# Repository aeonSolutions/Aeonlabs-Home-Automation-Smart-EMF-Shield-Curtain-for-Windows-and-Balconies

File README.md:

[ ](https://discord.gg/hw3j3RwfJf)

**Navigation** | [AeonLabs Main Index](https://github.com/aeonSolutions/aeonSolutions/blob/main/aeonSolutions-Main-Index.md)  >>  [Open Hardware Electronics](https://github.com/aeonSolutions/PCB-Prototyping-Catalogue)   >>   [Home-Automation](https://github.com/aeonSolutions/PCB-Prototyping-Catalogue/tree/main/Home-Automation)  >>  [Safety & Health](https://github.com/aeonSolutions/AeonLabs-Safety-Health)     >>  Smart EMF Shield Curtain for Windows and Balconies

<p align="right">
 <a href="https://github-com.translate.goog/aeonSolutions/Aeonlabs-Home-Automation-Smart-EMF-Shield-Curtain-for-Windows-and-Balconies?_x_tr_sl=en&_x_tr_tl=nl&_x_tr_hl=en&_x_tr_pto=wapp">Change language</a> <br>
Last update 07-09-2024 <br> <br>
partially sponsored by <br> 
    
</p>

⚠️ **Start by reading the documentation first**. [Click here to open it](https://github.com/aeonSolutions/AeonLabs-Safety-Health/wiki) 

# Smart EMF Shield Curtain for Windows and Balconies

<p align="left"> 
  
<b>Status:</b>
 Hardware electronics are Fully tested and working. The first 🥇 release of the firmware code is now available. <br>
&nbsp; Looking for someone available to collaborate on the firmware coding. If you like this project and want faster development, prototyping, and testing consider a donation or sponsoring. thank you 🙏.
 </p>

<p align="center">  
   
</p>

## The problem
nowadays many are sensitive to electromagnetic frequency radiation mainly due to excessive exposure above natural and healthy limits. There are many solutions to mitigate exposure to this kind of radiation however none have the ability to collect EMF energy values directly from a window or access door to a balcony.

## The idea
This smart device is intended to be installed and fixed into a copper electromagnetic (EM) shield on any EM indoor window or balcony door. It has the main ability to collect EM sensor data from the curtain itself and send it to a public data repository, for instance, a #dataverse (see www.dataverse.org)

<p align="center">
   <br>
   <sup> Figure 1- Example of a window in a room where this Smart Device can be installed</sup>
</p>

## Total Cost of this Project
The total cost of this project to date is listed below:
- Work hours dedicated to this project: >300 w.h <br>
  This includes research and study about Bio EM RF, building this repository, and other useless miscellaneous online tasks. <br>
  hardware electronics assembly and testing, several times.
- Electronic components  >200 eur
- Aluminium Enclosure Case and other materials ~20 eur ( [buy one on AliExpress ](https://s.click.aliexpress.com/e/_DkqC3wL) )

<p align="center">

</p>

See [here](https://github.com/aeonSolutions/AeonLabs-Safety-Health) who sponsored, to this date, the Safety & Health project. 

<br>

## Important Information
The smart safety & health solution is for the kind of wireless aggression that behaves like ripples in a pond. For instance Wireless electromagnetic radios, including those found on smartphones, tablets, wifi routers at home, and many more.

**This smart device is not able to detect wireless aggressions targeted to a person's body and individual. For instance, using some kind of beam-forming device or technologies**. For example, Laser and laser-like kind of devices and kind of technologies. 

**When installing this smart solution, take action and be conscious that the aggression/aggressor may change to other types and kinds of "wireless devices" this smart device is unable to detect**.  

**Always use this smart device connected to a public data repository with LIVE data streams. At the same time, notify the authorities immediately and provide the web address link where the public data repository can be found**. Data repositories based on Harvard's www.dataverse.org are currently the most suited (not ideal) for the smart solution provided. 

**Be advised**

Known open data repositories partially compatible with these smart devices:
- www.dataverse.org [partial compatible] (open firmware provided here uses a dataverse repository API)
- www.figshare.com [partial compatible]
- www.datadryad.org [not compatible; no API]

<br>

<p align="center">
     <br>
 <sup> Figure 2 - 3D rendering in KiCad of the hardware electronics </sup>
</p>

<p align="center">
<strong> <a href="https://aeonsolutions.github.io/sponsor/em_radiation/">Interactive view of the PCB Layout</a> </strong> &nbsp;
  <strong> <a href="https://aeonsolutions.github.io/sponsor/em_radiation//circuit_schematic.html">Interactive view of the circuit schematic</a> </strong> <br>
 <sup>Click to view the latest revision</sup>
</p>

This device is designed to burn out every time an electromagnetic pulse, spark, or other EMF has a too-high energy. This way the victim can use the burnt device as evidence when presenting a complaint to the authorities.

stay safe.

<p align="center">
    <br>
 <sup> Figure 3 - Smart EM Device Already Assemble and ready to be installed on the Aluminium Enclosure</sup>
</p>

## Compatibility

<p align="center">

</p>

###  Status
  Hardware electronics are Fully tested and working. The first 🥇 release of the firmware code is now available.

[January 1, 2024] - The firmware 1.0.0 for Over the Air Updates is now released to the public. Goto the [releases section](https://github.com/aeonSolutions/Aeonlabs-Home-Automation-Smart-EMF-Shield-Curtain-for-Windows-and-Balconies/releases/tag/openFirmware) to learn more.  

<br>

## OEM Firmware code
The OEM version of the firmware code can be found in the folder **OEM firmware code**.  It has by default OTA updates, meaning the smart concrete curing device automatically updates it self when newer updated versions are made available here.  

This code uses my own ESP32 C++ class libraries to expedite the development of the code of ESP32 microcontrollers. The repository is located in the [open source software section](https://github.com/aeonSolutions/aeonlabs-ESP32-C-Base-Firmware-Libraries#readme).

#### Send the collected sensor data to this repository
On this repository, there's a special folder, named [datasets](https://github.com/aeonSolutions/AeonLabs-Safety-Health/tree/main/Measurements/datasets), where anyone is able to upload dataset files directly from their open smart devices. This folder is intended to facilitate sharing of "electromagnetic" measurements among anyone with interest and capable of studying and analyzing it in search of EM anomalies to improve detection of the open hardware electronics made available here. **Anyone is invited to participate, cost-free**. 

&nbsp;&nbsp; To assist you with the firmware programming, there's a C++ test code compatible with all Arduino devices that anyone can use to speed up the programming of the open smart device. Here's the link: <br>
https://github.com/aeonSolutions/Aeonlabs-Arduino_Hardware_Test_Code/tree/main/github_api_test_upload <br>
Any questions on how to do it, send me a message on the Discord Server:

<div align="center">

[ ](https://discord.gg/hw3j3RwfJf)

</div>

<br>

## What one additionally needs
- [USB to UART/USB TTL firmware burner for 5V and 3.3V MCUs ](https://github.com/aeonSolutions/PCB-Prototyping-Catalogue/blob/main/DIY-Maker/README.md)
- [Radiation Shield Curtain](https://s.click.aliexpress.com/e/_DC76f4j) or any other conducting material or conductive glass window
  <p align="center"> 
 
</p>

- [4.2V Lipo Battery](https://s.click.aliexpress.com/e/_Dl3iRpl)
  
<br />
<br />

**Get a Notification on every PCB update**

|  | You can fill in your [email here (Google form)](https://docs.google.com/forms/d/e/1FAIpQLScErMgQYRdA-umvCjvTPPrCO7Lg1QYowTxb7vfa8cTfrcPEAA/viewform?usp=pp_url) and I'll send a reminder when a new PCB prototype is made available here or a new revision for an existing PCB. Stay tuned! |
|-------------|------|

<br>

<br />
<br />

## Author

You can get in touch with me on my LinkedIn Profile:

#### Miguel Tomas

You can also follow my GitHub Profile to stay updated about my latest projects: 

<br>

**Hire me** <br>
See [here](https://github.com/aeonSolutions/PCB-Prototyping-Catalogue/wiki/How-to-Hire-AeonLabs) how to hire AeonLabs.

<br>

### Be supportive of my dedication and work towards technology education and buy me a cup of coffee
The PCB design Files I provide here for anyone to use are free. If you like this Smart Device or use it, please consider buying me a cup of coffee, a slice of pizza, or a book to help me study, eat, and think new PCB design files.

<p align="center">
    
</p>

### Make a donation on PayPal
Make a donation on PayPal and get a TAX refund*.

<p align="center">
    
</p>

### Support all these open hardware projects and become a GitHub sponsor  
Did you like any of my PCB KiCad Designs? Help and Support my open work to all by becoming a GitHub sponsor.

<p align="center">

</p>

### License

Before proceeding to download any of AeonLabs open source code for software solutions and/or open hardware electronics for smart devices and data acquisition make sure you are choosing the right license for your project. See [AeonLabs Solutions for Open Hardware & Open Source Code](https://github.com/aeonSolutions/PCB-Prototyping-Catalogue/wiki/AeonLabs-Solutions-for-Open-Hardware-&-Source-Development) for more information. For commercial business solutions contact AeonLabs for more information ℹ️ using the contacts above. Thank you 🙏.

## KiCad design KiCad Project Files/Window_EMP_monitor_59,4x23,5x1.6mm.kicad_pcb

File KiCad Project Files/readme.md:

[PCB-Prototyping-Catalogue](https://github.com/aeonSolutions/PCB-Prototyping-Catalogue)  >>   [Home-Automation](https://github.com/aeonSolutions/PCB-Prototyping-Catalogue/tree/main/Home-Automation)  >>  [Home Automation Safety & Health](https://github.com/aeonSolutions/PCB-Prototyping-Catalogue/blob/main/Home%20Automation%20Safety%20%26%20Health/readme.md)   >>  Smart EMF Shield Curtain for Windows and Balconies

<p align="right">
 <a href="https://github-com.translate.goog/aeonSolutions/Aeonlabs-Home-Automation-Smart-EMF-Shield-Curtain-for-Windows-and-Balconies?_x_tr_sl=en&_x_tr_tl=nl&_x_tr_hl=en&_x_tr_pto=wapp">Change language</a> <br>
Last update 04-05-2024 <br> <br>
partially sponsored by <br> 
    
</p>

<br>

This folder contains the KiCad Project files, for the hardware electronics of the Smart EMF Shield Curtain for Windows and Balconies.  Each KiCad project is available with a [creative commons share alike non-commercial license](https://creativecommons.org/licenses/by-nc-sa/4.0/deed.en). 

<p align="center">
<strong> <a href="https://aeonsolutions.github.io/sponsor/em_radiation/">Interactive view of the PCB Layout</a> </strong> &nbsp;
  <strong> <a href="https://aeonsolutions.github.io/sponsor/em_radiation//circuit_schematic.html">Interactive view of the circuit schematic</a> </strong> <br>
 <sup>Click to view the latest revision</sup>
</p>

However, they're not fully complete. If you like it and are looking to use it on your projects, you can download the complete Kicad project files with a one-time donation, [click here](https://github.com/sponsors/aeonSolutions) to learn how,  and don't forget to include it in a message the name of the module/hardware electronics you need. <br> Thank you 🙏.

### Support all these open hardware projects and become a GitHub sponsor  
Did you like any of my PCB KiCad Designs? Help and Support my open work to all by becoming a GitHub sponsor.

<p align="center">

</p>

#

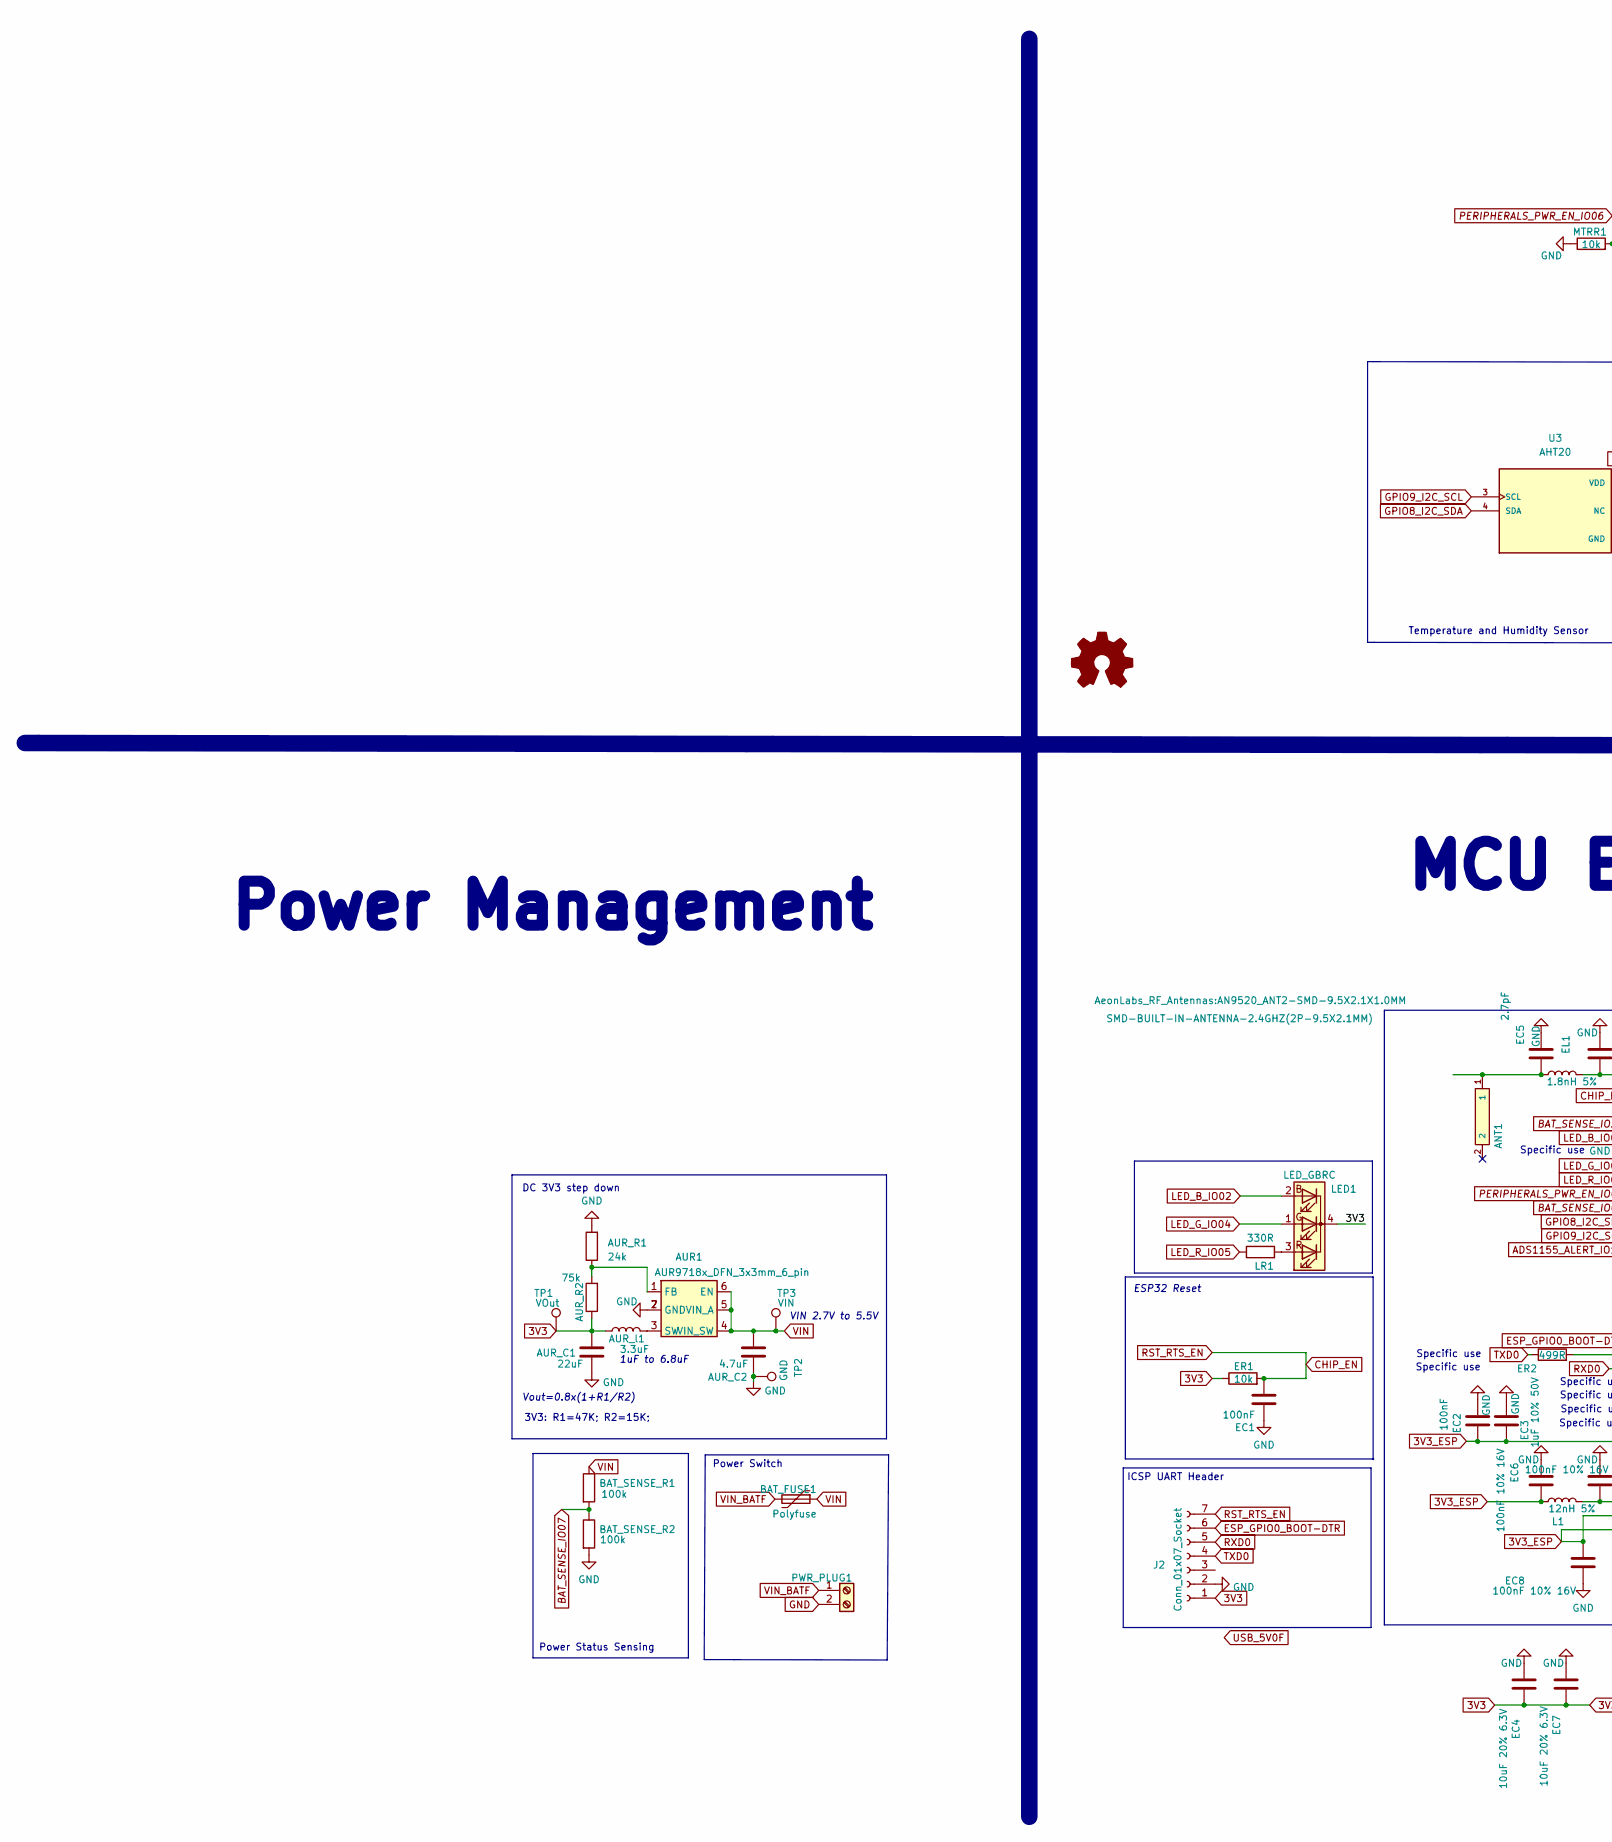
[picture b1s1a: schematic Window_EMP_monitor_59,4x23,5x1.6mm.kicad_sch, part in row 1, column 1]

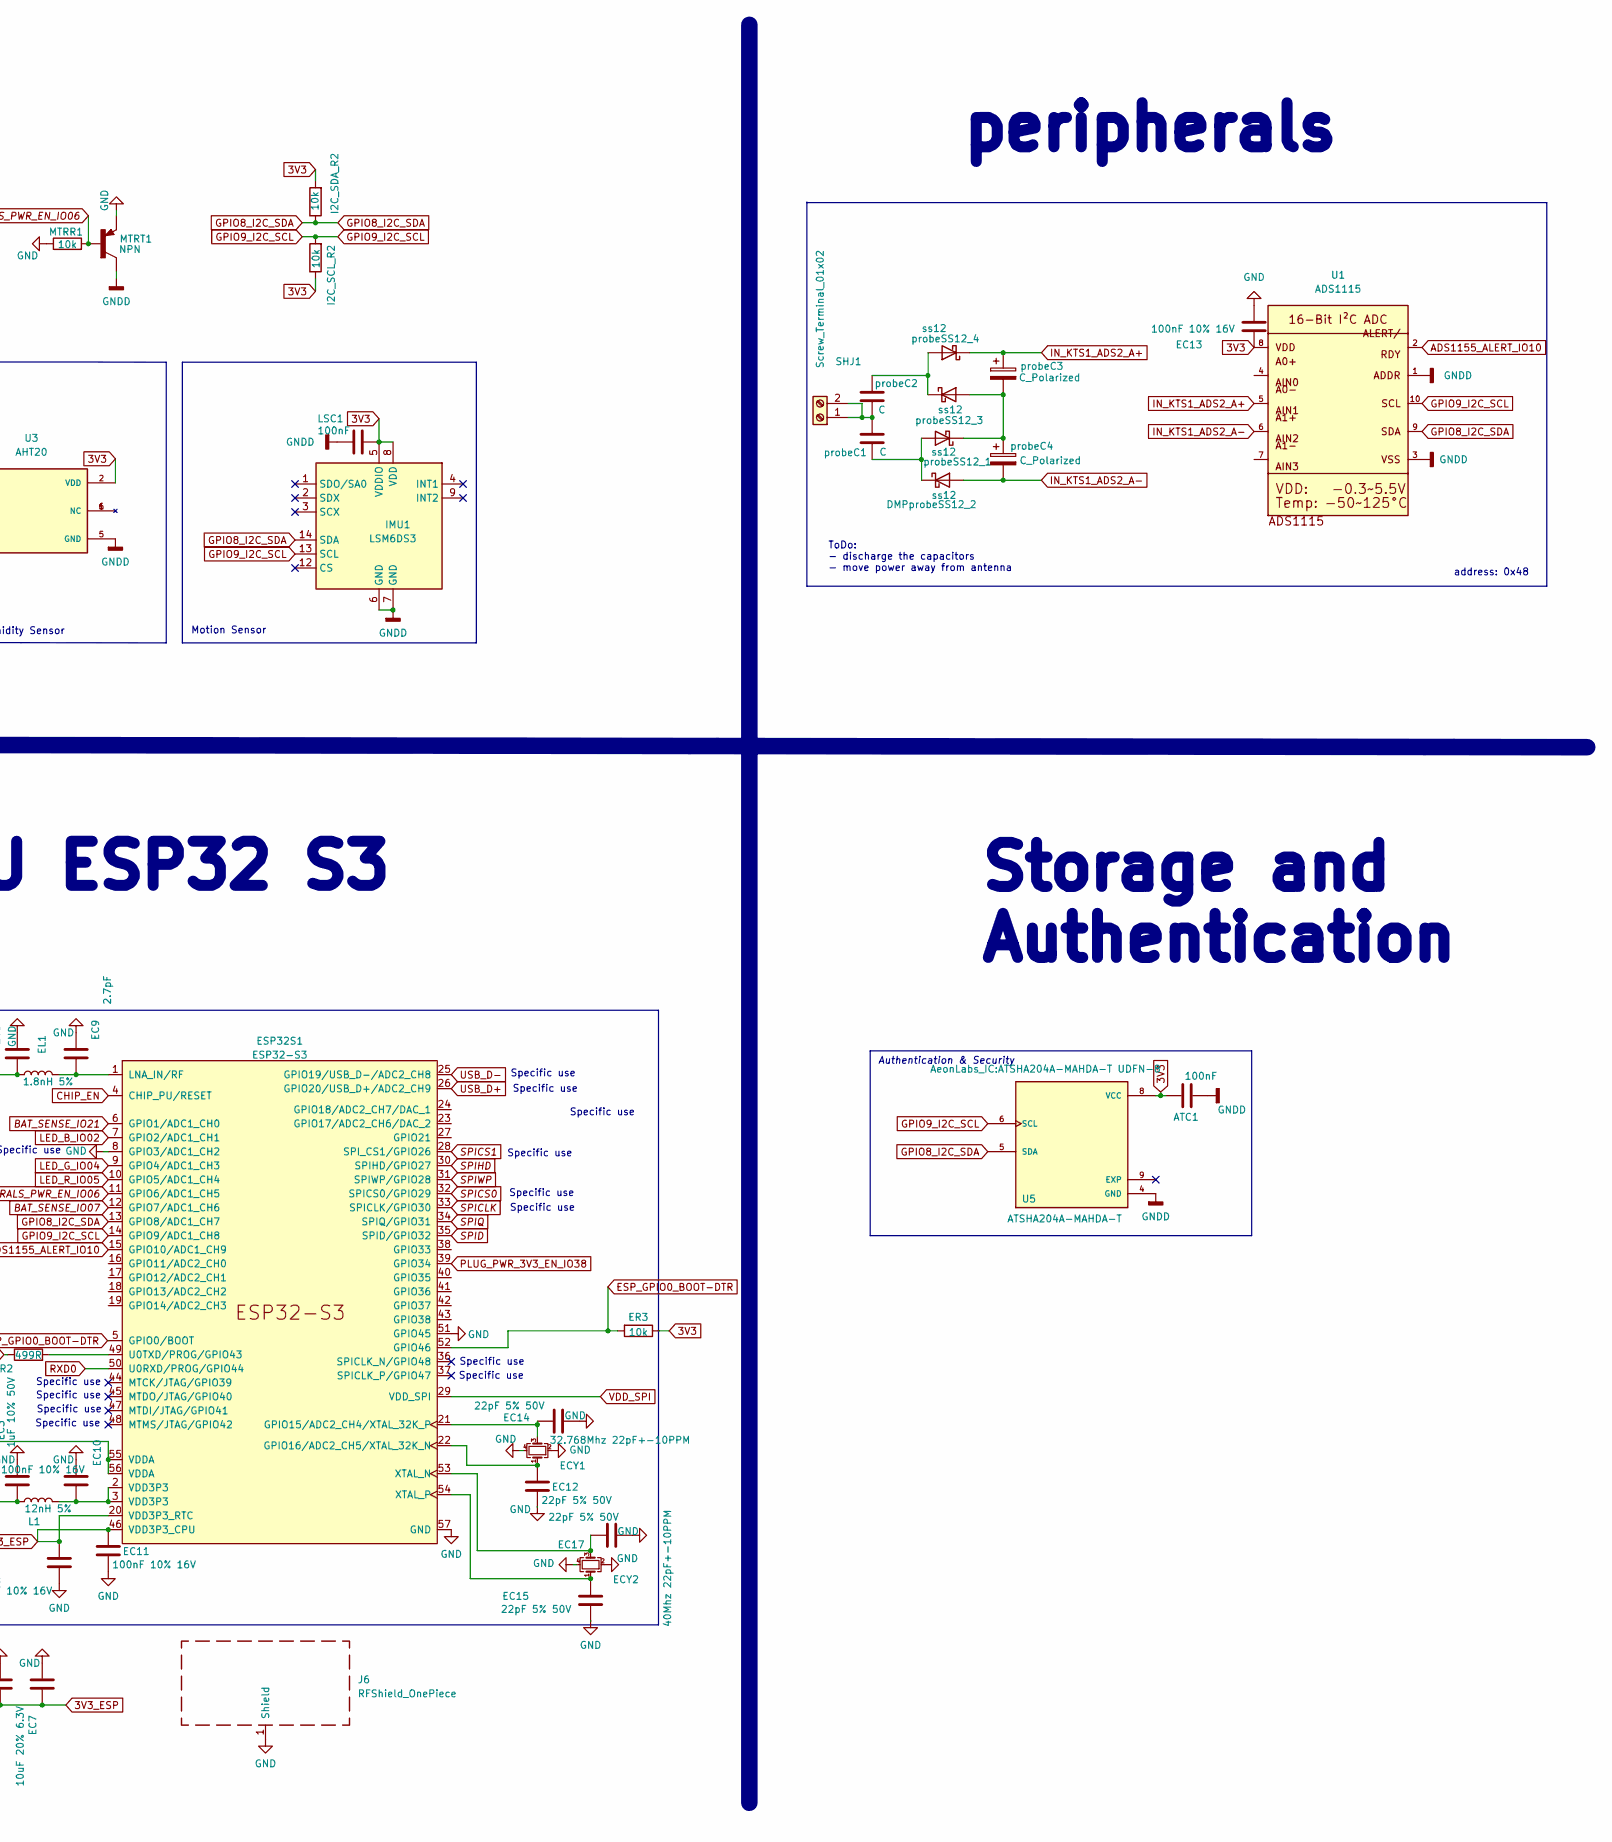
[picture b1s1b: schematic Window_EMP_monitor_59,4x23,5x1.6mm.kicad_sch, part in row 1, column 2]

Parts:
ANT1: SMD-BUILT-IN-ANTENNA-2.4GHZ(2P-9.5X2.1MM); AN9520_ANT2-SMD-9.5X2.1X1.0MM
ATC1: 100nF; C_0603_1608Metric
AUR1: AUR9718x_DFN_3x3mm_6_pin; AUR9718 ST1S09 SON95P300X300X100-7N
AUR_C1: 22uF; C_0805_2012Metric_Pad1.18x1.45mm_HandSolder
AUR_C2: 4.7uF; C_0805_2012Metric_Pad1.18x1.45mm_HandSolder
AUR_R1: 24k; R_0805_2012Metric_Pad1.20x1.40mm_HandSolder
AUR_R2: 75k; R_0805_2012Metric_Pad1.20x1.40mm_HandSolder
AUR_l1: 3.3uF; L_1210_3225Metric
BAT_FUSE1: Polyfuse; Fuse_1206_3216Metric_Pad1.42x1.75mm_HandSolder
BAT_SENSE_R1, BAT_SENSE_R2: 100k; R_0603_1608Metric
DMPprobeSS12_2: ss12; D_1206_3216Metric
EC1, EC2: 100nF; C_0603_1608Metric
EC3: 1uF 10% 50V; C_0805_2012Metric
EC4, EC7: 10uF 20% 6.3V; C_0805_2012Metric
EC5, EC9: 2.7pF; C_0603_1608Metric
EC6, EC8, EC10, EC11, EC13: 100nF 10% 16V; C_0603_1608Metric
EC12, EC14, EC15, EC17: 22pF 5% 50V; C_0603_1608Metric
ECY1: 32.768Mhz 22pF+-10PPM; Crystal_SMD_3225-4Pin_3.2x2.5mm
ECY2: 40Mhz 22pF+-10PPM; Crystal_SMD_3225-4Pin_3.2x2.5mm
EL1: 1.8nH 5%; L_0805_2012Metric
ER1, ER3: 10k; R_0603_1608Metric
ER2: 499R; R_0603_1608Metric
ESP32S1: ESP32-S3; QFN-56-1EP_7x7mm_P0.4mm_EP5.6x5.6mm
I2C_SCL_R2, I2C_SDA_R2: 10k; R_0603_1608Metric
IMU1: LSM6DS3; LSM6DS3 PQFN50P300X250X86-14N
J2: Conn_01x07_Socket; SOIC_clipProgSmall
J6: RFShield_OnePiece; ESP32-S3 GND Shield
L1: 12nH 5%; L_0805_2012Metric
LED1: LED_GBRC; LED_1206_3210_RGB_Metric
LR1: 330R; R_0603_1608Metric
LSC1: 100nF; C_0603_1608Metric
MTRR1: 10k; R_0805_2012Metric
MTRT1: NPN; SOT-23; PARTREV C2001
PWR_PLUG1: Screw_Terminal_01x02; JST_EH_S2B-EH_1x02_P2.50mm_Horizontal
SHJ1: Screw_Terminal_01x02; JST_SH_SM02B-SRSS-TB_1x02-1MP_P1.00mm_Horizontal
TP1: VOut; TestPoint_Pad_D1.0mm
TP2: GND; TestPoint_Pad_D1.0mm
TP3: VIN; TestPoint_Pad_D1.0mm
U1: ADS1115; ASD1155
U3: AHT20; AHT20 PSON100P300X300X110-6N; PARTREV V1.0
U5: ATSHA204A-MAHDA-T; ATSHA204A-MAHDA-T UDFN-8; PART_REV A
probeC1, probeC2: C; CP_EIA-7343-31_Kemet-D
probeC3, probeC4: C_Polarized; CP_Radial_D5.0mm_P2.50mm
probeSS12_1, probeSS12_3, probeSS12_4: ss12; D_1206_3216Metric

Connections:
3V3: ATC1.2, AUR_C1.1, AUR_R2.1, AUR_l1.1, EC2.2, EC3.2, EC4.1, EC6.1, EC7.1, EC8.1, EC11.1, EC13.2, ER1.1, ER3.1, ESP32S1.20 (VDD3P3_RTC), ESP32S1.46 (VDD3P3_CPU), ESP32S1.55 (VDDA), ESP32S1.56 (VDDA), I2C_SCL_R2.1, I2C_SDA_R2.2, IMU1.5 (VDDIO), IMU1.8 (VDD), J2.1, L1.1, LED1.4 (K), LSC1.1, TP1.1, U1.8, U3.2 (VDD), U5.8 (VCC)
ADS1155_ALERT_IO10: ESP32S1.15 (GPIO10/ADC1_CH9), U1.2
BAT_SENSE_IO07: BAT_SENSE_R1.2, BAT_SENSE_R2.1, ESP32S1.12 (GPIO7/ADC1_CH6)
BAT_SENSE_IO21: ESP32S1.6 (GPIO1/ADC1_CH0)
CHIP_EN: EC1.2, ER1.2, ESP32S1.4 (CHIP_PU/RESET), J2.7
ESP_GPIO0_BOOT-DTR: ER3.2, ESP32S1.5 (GPIO0/BOOT), ESP32S1.52 (GPIO46), J2.6
GND: AUR1.2 (GND), AUR1.7 (GND), AUR_C1.2, AUR_C2.2, AUR_R1.2, BAT_SENSE_R2.2, EC1.1, EC2.1, EC3.1, EC4.2, EC5.2, EC6.2, EC7.2, EC8.2, EC9.2, EC10.2, EC11.2, EC12.2, EC13.1, EC14.2, EC15.2, EC17.2, ECY1.2, ECY1.4, ECY2.2, ECY2.4, ESP32S1.8 (GPIO3/ADC1_CH2), ESP32S1.51 (GPIO45), ESP32S1.57 (GND), J2.2, MTRR1.1, MTRT1.2, PWR_PLUG1.2, TP2.1
GNDD: ATC1.1, IMU1.6 (GND), IMU1.7 (GND), LSC1.2, MTRT1.3, U1.1, U1.3, U3.5 (GND), U5.4 (GND)
GPIO8_I2C_SDA: ESP32S1.13 (GPIO8/ADC1_CH7), I2C_SDA_R2.1, IMU1.14 (SDA), U1.9, U3.4 (SDA), U5.5 (SDA)
GPIO9_I2C_SCL: ESP32S1.14 (GPIO9/ADC1_CH8), I2C_SCL_R2.2, IMU1.13 (SCL), U1.10, U3.3 (SCL), U5.6 (SCL)
IN_KTS1_ADS2_A+: U1.5, probeC3.1, probeSS12_4.1 (K)
IN_KTS1_ADS2_A-: DMPprobeSS12_2.2 (A), U1.6, probeC4.2
LED_B_IO02: ESP32S1.7 (GPIO2/ADC1_CH1), LED1.2 (BA)
LED_G_IO04: ESP32S1.9 (GPIO4/ADC1_CH3), LED1.1 (GA)
LED_R_IO05: ESP32S1.10 (GPIO5/ADC1_CH4), LR1.1
unnamed: ANT1.1, EC5.1, EL1.1
unnamed: AUR1.1 (FB), AUR_R1.1, AUR_R2.2
unnamed: AUR1.3 (SW), AUR_l1.2
unnamed: DMPprobeSS12_2.1 (K), probeC1.2, probeSS12_1.2 (A)
unnamed: EC10.1, ESP32S1.2 (VDD3P3), ESP32S1.3 (VDD3P3), L1.2
unnamed: EC14.1, ECY1.3, ESP32S1.21 (GPIO15/ADC2_CH4/XTAL_32K_P)
unnamed: EC12.1, ECY1.1, ESP32S1.22 (GPIO16/ADC2_CH5/XTAL_32K_N)
unnamed: EC9.1, EL1.2, ESP32S1.1 (LNA_IN/RF)
unnamed: ER2.2, ESP32S1.49 (U0TXD/PROG/GPIO43)
unnamed: EC17.1, ECY2.3, ESP32S1.53 (XTAL_N)
unnamed: EC15.1, ECY2.1, ESP32S1.54 (XTAL_P)
unnamed: LED1.3 (RA), LR1.2
unnamed: SHJ1.1, SHJ1.2, probeC1.1, probeC2.2
unnamed: probeC3.2, probeC4.1, probeSS12_1.1 (K), probeSS12_3.2 (A)
unnamed: probeC2.1, probeSS12_3.1 (K), probeSS12_4.2 (A)
PERIPHERALS_PWR_EN_IO06: ESP32S1.11 (GPIO6/ADC1_CH5), MTRR1.2, MTRT1.1
PLUG_PWR_3V3_EN_IO38: ESP32S1.39 (GPIO34)
RXD0: ESP32S1.50 (U0RXD/PROG/GPIO44), J2.5
SPICLK: ESP32S1.33 (SPICLK/GPIO30)
SPICS0: ESP32S1.32 (SPICS0/GPIO29)
SPICS1: ESP32S1.28 (SPI_CS1/GPIO26)
SPID: ESP32S1.35 (SPID/GPIO32)
SPIHD: ESP32S1.30 (SPIHD/GPIO27)
SPIQ: ESP32S1.34 (SPIQ/GPIO31)
SPIWP: ESP32S1.31 (SPIWP/GPIO28)
TXD0: ER2.1, J2.4
USB_D+: ESP32S1.26 (GPIO20/USB_D+/ADC2_CH9)
USB_D-: ESP32S1.25 (GPIO19/USB_D-/ADC2_CH8)
VDD_SPI: ESP32S1.29 (VDD_SPI)
VIN: AUR1.4 (VIN_SW), AUR1.5 (VIN_A), AUR1.6 (EN), AUR_C2.1, BAT_FUSE1.1, BAT_SENSE_R1.1, TP3.1
VIN_BATF: BAT_FUSE1.2, PWR_PLUG1.1

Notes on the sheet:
Specific use
peripherals
DC 3V3 step down
Power Switch
address: 0x48
Temperature and Humidity Sensor
Power Status Sensing
ToDo: - discharge the capacitors - move power away from antenna
Vout=0.8x(1+R1/R2)
Motion Sensor
ESP32 Reset
1uF to 6.8uF
Storage and Authentication
Power Management
ICSP UART Header
MCU ESP32 S3
Authentication & Security
VIN 2.7V to 5.5V
3V3: R1=47K; R2=15K;

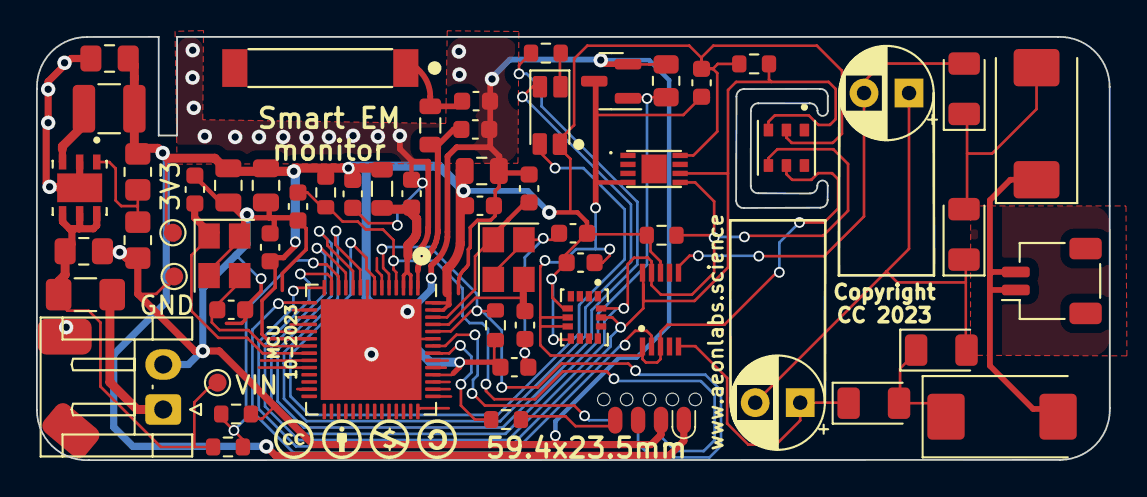
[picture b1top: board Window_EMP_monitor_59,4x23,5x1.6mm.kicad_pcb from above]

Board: 2 copper layers, 59.6 x 23.5 mm, 60 parts (0 on the bottom side), 34 nets.
